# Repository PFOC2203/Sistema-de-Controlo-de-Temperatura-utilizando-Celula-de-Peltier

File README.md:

# Sistema-de-Controlo-de-Temperatura-utilizando-C-lula-de-Peltier
"Sistema IoT de controlo de temperatura com ESP32C3, Célula de Peltier e interface Web.

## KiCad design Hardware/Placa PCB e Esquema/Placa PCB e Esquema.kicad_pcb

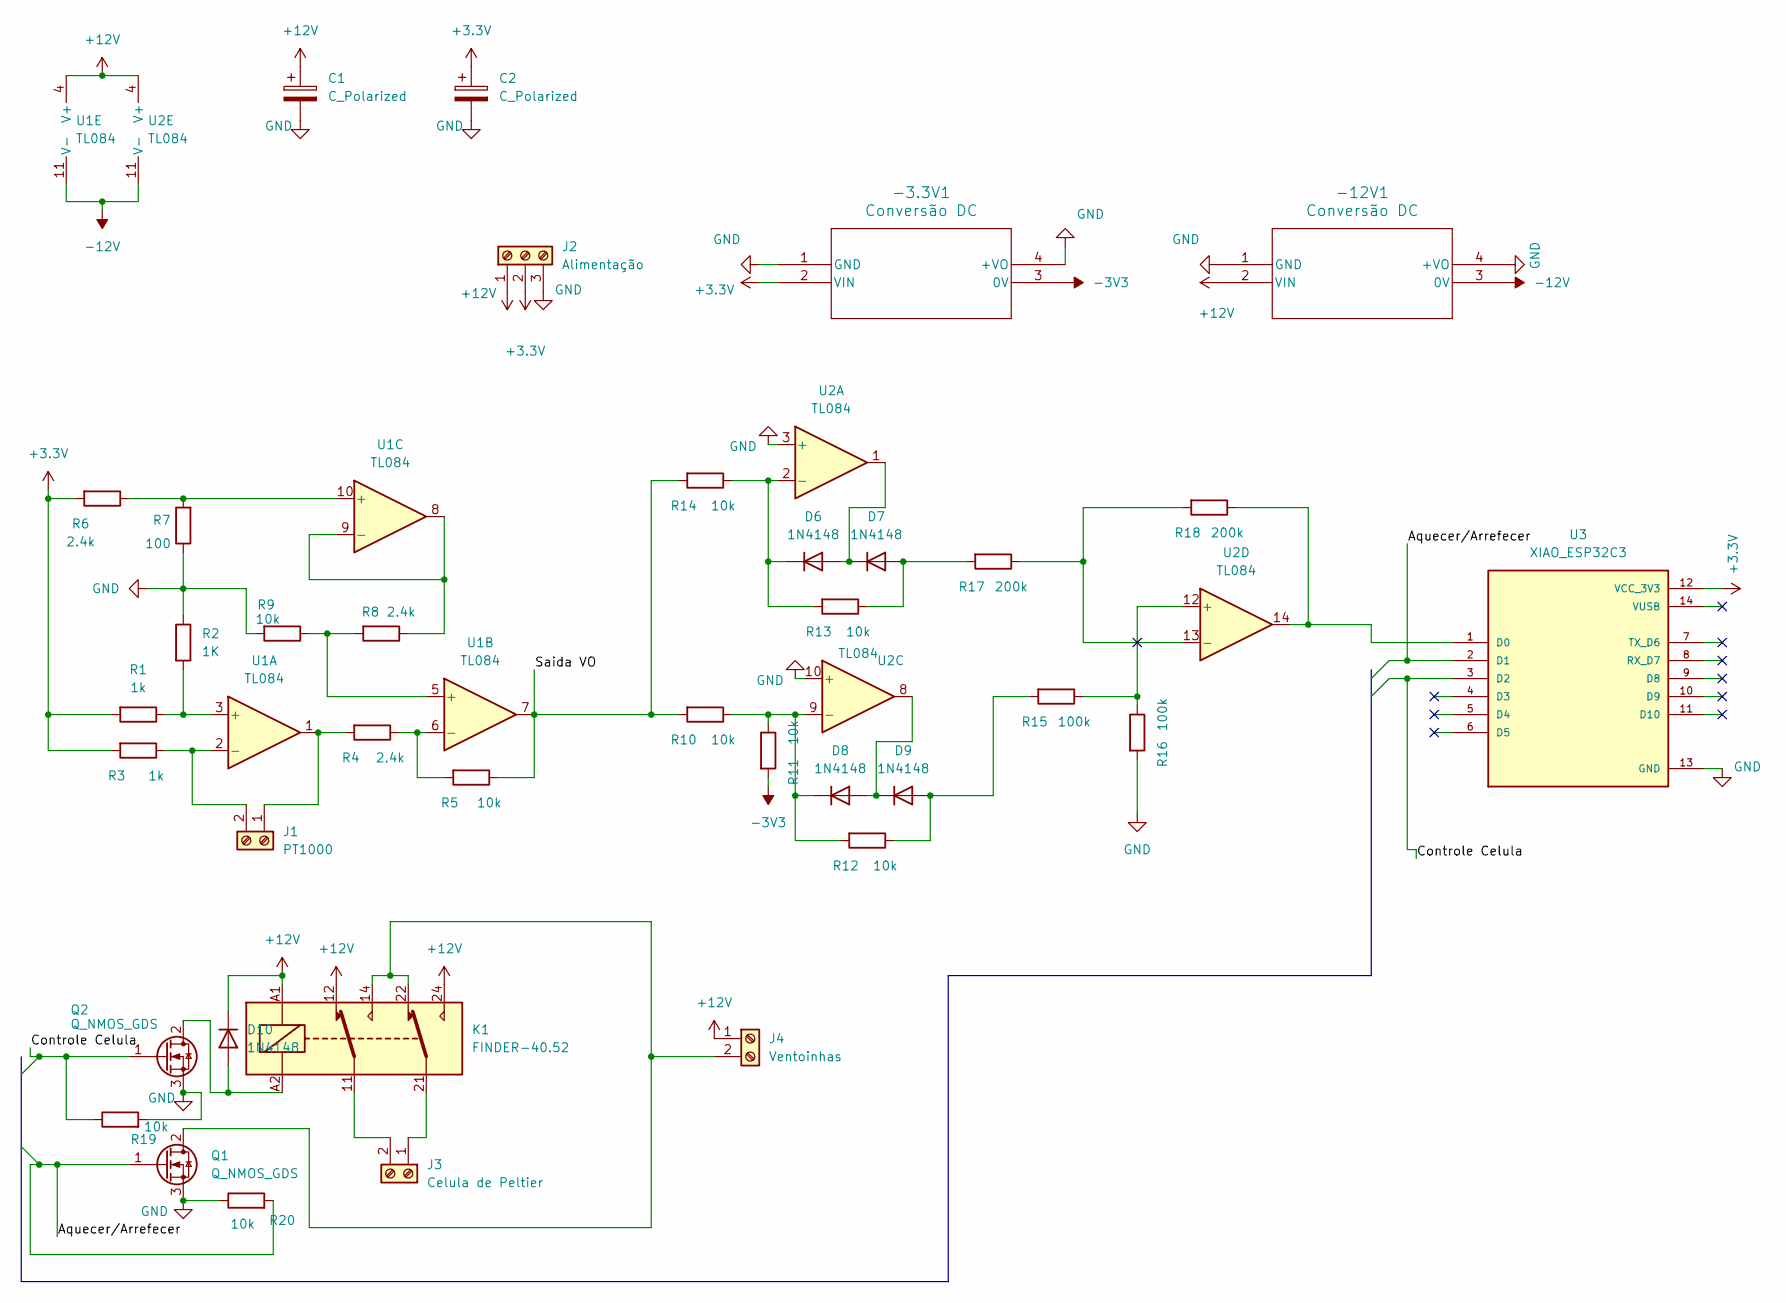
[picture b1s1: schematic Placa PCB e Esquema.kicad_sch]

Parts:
-3.3V1, -12V1: Conversão DC; Converter_DCDC_RECOM_R-78S-0.1_THT
C1, C2: C_Polarized; CP_Radial_Tantal_D5.5mm_P5.00mm
D6, D7, D8, D9, D10: 1N4148; D_DO-35_SOD27_P3.81mm_Vertical_CathodeUp
J1: PT1000; TerminalBlock_Phoenix_PT-1,5-2-5.0-H_1x02_P5.00mm_Horizontal
J2: Alimentação; TerminalBlock_Phoenix_MKDS-1,5-3_1x03_P5.00mm_Horizontal
J3: Celula de Peltier; TerminalBlock_Phoenix_MKDS-3-2-5.08_1x02_P5.08mm_Horizontal
J4: Ventoinhas; TerminalBlock_Phoenix_MKDS-3-2-5.08_1x02_P5.08mm_Horizontal
K1: FINDER-40.52; Relay_DPDT_Finder_40.52
Q1, Q2: Q_NMOS_GDS; TO-220-3_Horizontal_TabDown
R1, R3: 1k; R_Axial_DIN0204_L3.6mm_D1.6mm_P7.62mm_Horizontal
R2: 1K; R_Axial_DIN0204_L3.6mm_D1.6mm_P7.62mm_Horizontal
R4, R6, R8: 2.4k; R_Axial_DIN0204_L3.6mm_D1.6mm_P7.62mm_Horizontal
R5, R9, R10, R11, R12, R13, R14, R19, R20: 10k; R_Axial_DIN0204_L3.6mm_D1.6mm_P7.62mm_Horizontal
R7: 100; R_Axial_DIN0204_L3.6mm_D1.6mm_P7.62mm_Horizontal
R15, R16: 100k; R_Axial_DIN0204_L3.6mm_D1.6mm_P7.62mm_Horizontal
R17, R18: 200k; R_Axial_DIN0204_L3.6mm_D1.6mm_P7.62mm_Horizontal
U1, U2: TL084; DIP-14_W7.62mm
U3: XIAO_ESP32C3; MODULE_XIAO_ESP32C3; PARTREV 23/05/2022

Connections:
+3.3V: -3.3V1.2 (VIN), C2.1, J2.2, R1.2, R3.2, R6.2, U3.12 (VCC_3V3)
+12V: -12V1.2 (VIN), C1.1, D10.1 (K), J2.1, J4.1, K1.12, K1.24, K1.A1, U1.4 (V+), U2.4 (V+)
-3V3: -3.3V1.3 (0V), R11.2
-12V: -12V1.3 (0V), U1.11 (V-), U2.11 (V-)
/Aquecer/Arrefecer: Q1.1 (G), R20.2, U3.2 (D1)
/Controle Celula: Q2.1 (G), R19.1, U3.3 (D2)
/Saida VO: R5.1, R10.2, R14.2, U1.7
GND: -3.3V1.1 (GND), -3.3V1.4 (+VO), -12V1.1 (GND), -12V1.4 (+VO), C1.2, C2.2, J2.3, Q1.3 (S), Q2.3 (S), R2.1, R7.1, R9.2, R16.2, R19.2, R20.1, U2.3 (+), U2.10 (+), U3.13 (GND)
unnamed: D6.2 (A), D7.1 (K), U2.1
unnamed: D6.1 (K), R13.2, R14.1, U2.2 (-)
unnamed: D7.2 (A), R13.1, R17.2
unnamed: D8.2 (A), D9.1 (K), U2.8
unnamed: D8.1 (K), R10.1, R11.1, R12.2, U2.9 (-)
unnamed: D9.2 (A), R12.1, R15.2
unnamed: D10.2 (A), K1.A2, Q2.2 (D)
unnamed: J1.1, R4.2, U1.1
unnamed: J1.2, R3.1, U1.2 (-)
unnamed: J3.1, K1.21
unnamed: J3.2, K1.11
unnamed: J4.2, K1.14, K1.22, Q1.2 (D)
unnamed: R1.1, R2.2, U1.3 (+)
unnamed: R8.2, R9.1, U1.5 (+)
unnamed: R4.1, R5.2, U1.6 (-)
unnamed: R6.1, R7.2, U1.10 (+)
unnamed: R8.1, U1.8, U1.9 (-)
unnamed: R15.1, R16.1, U2.12 (+)
unnamed: R17.1, R18.2, U2.13 (-)
unnamed: R18.1, U2.14, U3.1 (D0)

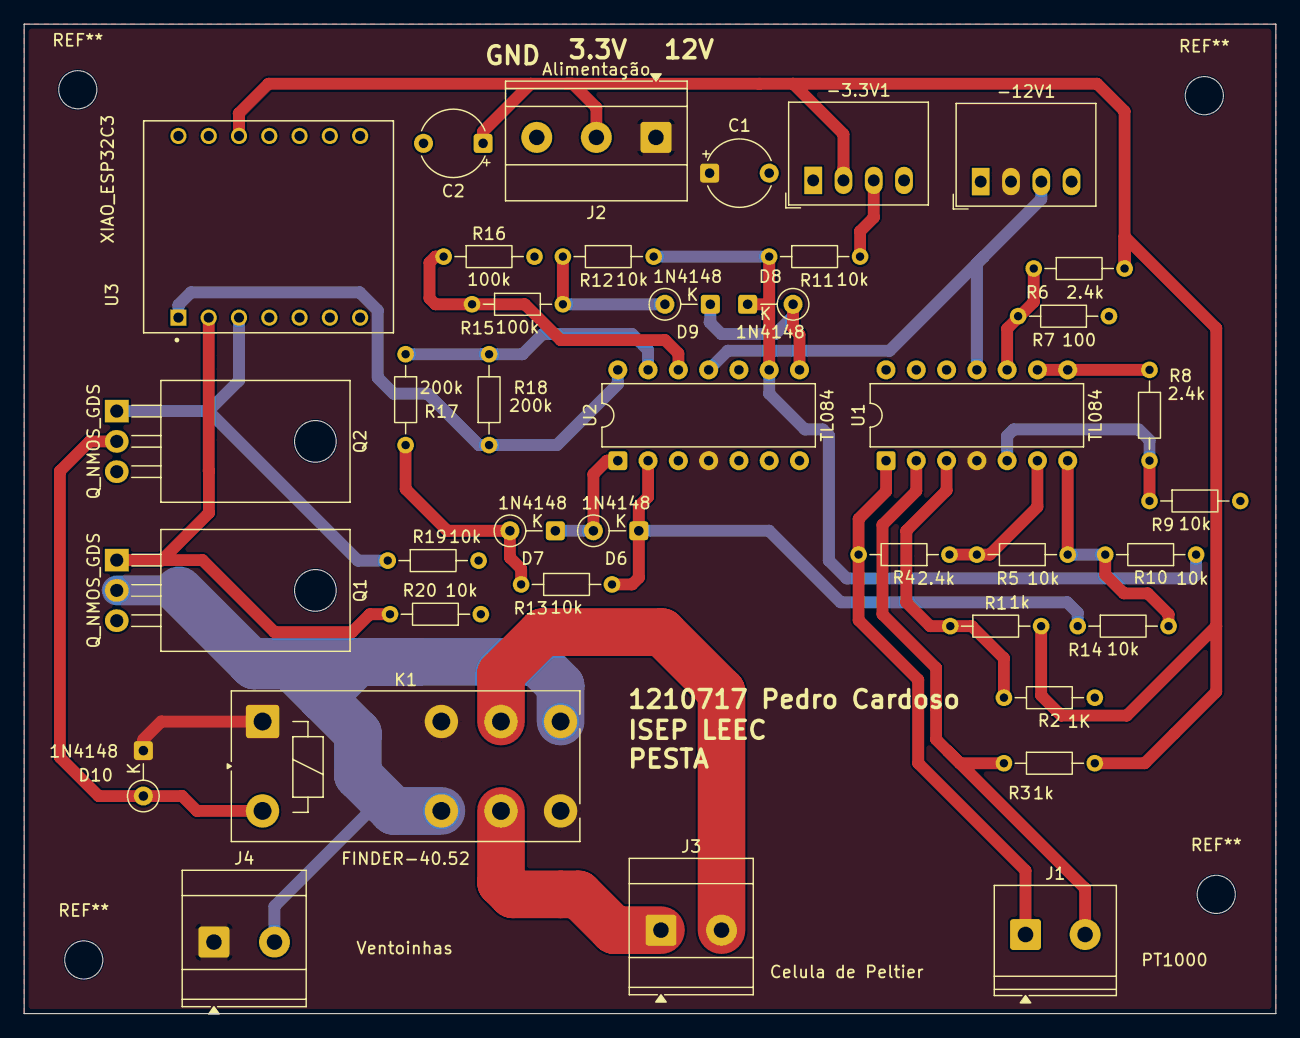
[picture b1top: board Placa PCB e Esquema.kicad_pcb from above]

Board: 2 copper layers, 105.0 x 83.0 mm, 39 parts (0 on the bottom side), 28 nets.

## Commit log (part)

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2026-06-28 Primeiro commit: Adiciona hardware KiCad e software do termóstato
2026-06-30 Prototipo Funcional V1
